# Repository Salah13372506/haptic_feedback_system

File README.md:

# Système de Retour Haptique avec Vision par Ordinateur

## Description du Projet

Projet réalisé dans le cadre du Master Systems for Rehabilitation (MSR) - Sorbonne Université.

Ce système d'assistance innovant a été conçu pour aider les personnes non-voyantes dans leur déplacement quotidien. Il combine la vision par ordinateur et le retour haptique pour détecter les obstacles et communiquer leur position à l'utilisateur via des vibrations. Développé initialement comme un système d'évitement d'obstacles, le projet a le potentiel d'évoluer vers une solution complète de navigation assistée.
Le système utilise une caméra de profondeur OAK-D pour détecter les obstacles et transmet l'information via des moteurs vibrants positionnés de manière ergonomique, permettant à l'utilisateur de percevoir intuitivement la direction des obstacles et de choisir un chemin sûr.
Ce projet s'inscrit dans une démarche d'innovation technologique au service de l'autonomie des personnes en situation de handicap visuel.

## Table des Matières

1. [Vue d'ensemble](#vue-densemble)
2. [Installation](#installation)
3. [Configuration de l'Espace de Travail](#configuration-de-lespace-de-travail)
4. [Nœuds ROS2](#nœuds-ros2)
5. [Partie Électronique](#partie-électronique)
6. [Partie Mécanique](#partie-mécanique)
7. [Documentation Utilisateur](#documentation-utilisateur)

## Vue d'ensemble

Ce projet implémente un système de détection d'obstacles et de retour haptique guidé par vision par ordinateur. Il utilise ROS2, une caméra de profondeur OAK-D, et des moteurs vibrants LRA (Linear Resonant Actuator) contrôlés par une carte Arduino MKR WiFi 1010.

## Installation

### Prérequis Système
- Ubuntu 22.04 LTS
- Python 3.10 ou supérieur
- Git
- VS Code avec PlatformIO

### ROS2 Humble
```bash
wget -c https://raw.githubusercontent.com/ros/rosdistro/master/ros.key && sudo apt-key add ros.key && sudo sh -c 'echo "deb [arch=amd64] http://packages.ros.org/ros2/ubuntu jammy main" > /etc/apt/sources.list.d/ros2.list' && sudo apt update && sudo apt install ros-humble-desktop-full
```

### Configuration Caméra OAK-D

1. Documentation officielle :
   - [Documentation Luxonis OAK-D](https://docs.luxonis.com/projects/api/en/latest/)
   - [Exemples DepthAI](https://github.com/luxonis/depthai-python/tree/main/examples)

2. Installation des dépendances :
   ```bash
   # Installation des dépendances système DepthAI
   sudo wget -qO- https://docs.luxonis.com/install_dependencies.sh | bash

   # Installation de la bibliothèque Python DepthAI
   python3 -m pip install depthai

   # Installation des dépendances ROS2
   sudo apt install ros-humble-depthai-ros
   ```

3. Test de l'installation :
   ```bash
   # Cloner les exemples
   git clone https://github.com/luxonis/depthai-python.git
   cd depthai-python/examples
   
   # Installer les dépendances Python
   python3 install_requirements.py
   
   # Tester la caméra
   python3 ColorCamera/rgb_preview.py
   ```

4. Vérification des règles udev :
   ```bash
   # Vérifier que la caméra est détectée
   lsusb | grep MyriadX
   
   # Si nécessaire, recharger les règles udev
   sudo udevadm control --reload-rules
   sudo udevadm trigger
   ```

### Configuration Arduino et PlatformIO (À lancer avant ROS2)

1. Installation de l'environnement de développement :
   ```bash
   # Installation de VS Code
   sudo apt update
   sudo apt install software-properties-common apt-transport-https wget
   wget -q https://packages.microsoft.com/keys/microsoft.asc -O- | sudo apt-key add -
   sudo add-apt-repository "deb [arch=amd64] https://packages.microsoft.com/repos/vscode stable main"
   sudo apt update
   sudo apt install code
   ```

2. Configuration de PlatformIO :
   - Ouvrir VS Code
   - Aller dans Extensions (Ctrl+Shift+X)
   - Rechercher "PlatformIO IDE"
   - Installer l'extension
   - Redémarrer VS Code

3. Structure du projet Arduino :
   ```
   haptic-arduino/
   ├── platformio.ini
   ├── src/
   │   └── main.cpp              # Code principal Arduino
   ├── lib/
   │   ├── Haptic_DRV2605/      # Bibliothèque des moteurs
   │   └── README.md
   └── include/
       └── README.md
   ```

4. Configuration détaillée dans `platformio.ini` :
   ```ini
   [env:mkrwifi1010]
   platform = atmelsam
   board = mkrwifi1010
   framework = arduino
   
   ; Configuration moniteur série
   monitor_speed = 115200
   monitor_flags = 
       --parity
       N
       --encoding
       UTF-8
   
   ; Dépendances externes
   lib_deps =
       arduino-libraries/WiFiNINA @ ^1.8.14
       bblanchon/ArduinoJson @ ^6.21.3
       Wire
       adafruit/Adafruit DRV2605 Library @ ^1.1.2
   
   ; Options de build
   build_flags =
       -D DEBUG_MODE
       -D WIFI_SSID=\"HapticArduino\"
       -D WIFI_PASS=\"haptic123\"
   
   ; Configuration mémoire
   board_build.f_cpu = 48000000L
   upload_speed = 115200
   ```

5. Compilation et téléversement :
   ```bash
   # Dans le dossier du projet Arduino
   pio run -t upload
   ```

6. Vérification du fonctionnement :
   ```bash
   # Ouvrir le moniteur série
   pio device monitor
   ```
   - Vérifier que l'Arduino crée bien le point d'accès WiFi
   - Confirmer l'initialisation des moteurs
   - Noter l'adresse IP (par défaut 192.168.4.1)

## Nœuds ROS2

### Objectifs des Nœuds

#### 1. Nœud Processeur de Profondeur (processor_node.py)
Ce nœud reçoit les données brutes de la caméra de profondeur et les traite pour identifier les obstacles.
Il normalise les données de profondeur et publie une image traitée où les obstacles proches sont plus sombres.

#### 2. Nœud de Projection 2D (2d.py)
Ce nœud transforme l'image de profondeur traitée en une projection 2D avec détection d'obstacles.
Il analyse la position des obstacles et détermine de quel côté l'utilisateur doit se diriger.

#### 3. Nœud de Publication Haptique (haptic_publisher.py)
Ce nœud gère l'activation des différents moteurs haptiques selon les commandes reçues.
Il maintient deux groupes de moteurs (gauche et droite) et coordonne leurs activations.

#### 4. Nœud Bridge WiFi (wifi_bridge.py)
Ce nœud établit la communication WiFi entre ROS2 et l'Arduino.
Il convertit les commandes ROS2 en messages JSON et les envoie à l'Arduino via UDP.

### Lancement des Nœuds

#### 1. Lancement de la Caméra
```bash
# Lance la caméra OAK-D et publie les données de profondeur
colcon build --symlink-install --packages-select depthai_bridge
colcon build --symlink-install --packages-select depthai_examples
source install/setup.bash
ros2 launch depthai_examples stereo_inertial_node.launch.py depth:=true
```

#### 2. Lancement des Nœuds de Traitement
```bash
# Compile et lance les nœuds de traitement de profondeur
colcon build --packages-select depth_processor
source install/setup.bash
ros2 run depth_processor processor_node
ros2 run depth_processor 2d_node
```

#### 3. Lancement des Nœuds Haptiques
```bash
# Compile et lance les nœuds de contrôle haptique
colcon build --packages-select haptic_control_interfaces haptic_control_pkg
source install/setup.bash
ros2 run haptic_control_pkg haptic_publisher
ros2 run haptic_control_pkg haptic_bridge
```

### Tests Rapides
```bash
# Active les moteurs gauches
ros2 topic pub /haptic_side haptic_control_interfaces/msg/SideCommand "{side: 2}"

# Active les moteurs droits
ros2 topic pub /haptic_side haptic_control_interfaces/msg/SideCommand "{side: 1}"
```

## Partie Électronique

### Liste du Matériel
- 1x Arduino MKR WiFi 1010
- 8x Moteurs LRA
- 1x Multiplexeur I2C TCA9548A
- 8x Drivers DRV2605
- 1x PCB personnalisée
- Composants:
  - Régulateur 3.3V
  - Condensateurs de découplage
  - Résistances pull-up
  - Connecteurs moteurs

### Carte PCB

La carte PCB a été conçue pour gérer 6 moteurs haptiques de type LRA. Elle intègre les composants suivants :

#### Composants Principaux
- 1x Arduino MKR WiFi 1010 (microcontrôleur principal)
- 6x Drivers DRV2605 (contrôle des moteurs LRA)
- 1x Multiplexeur I2C TCA9548A (gestion des multiples drivers)
- 6x Connecteurs JST femelles (connexion des moteurs)

#### Connexions
- Chaque moteur se connecte via un connecteur JST 2 pins pour :
  - VCC (alimentation)
  - GND (masse)

#### Communication
- Bus I2C distribué via le multiplexeur
- Le multiplexeur permet de gérer les 6 drivers avec une seule paire de lignes I2C

*Note : Tous les fichiers liés à la PCB sont disponibles dans le dossier `PCB_designing/` du projet*

### Configuration WiFi Arduino
- Mode: Point d'accès (AP)
- SSID: "HapticArduino"
- Password: "haptic123"
- IP Arduino: 192.168.4.1
- Port UDP: 8888
- Format: JSON

### Format des Messages JSON
```json
{
    "motor": 0-7,           // ID du moteur
    "waveform": 0-123,      // Pattern de vibration
    "activate": true/false,  // Activation/désactivation
    "intensity": 0.0-1.0    // Intensité de vibration
}
```

## Partie Mécanique

Le système comporte plusieurs pièces imprimées en 3D, chacune ayant une fonction spécifique :

### 1. Support Principal
- Pièce servant de base au système
- Conçue avec un système de clips pour maintenir la PCB
- Intègre un couvercle arrière pour protéger l'électronique
- Dimensions optimisées pour s'adapter à la PCB et au boîtier de la caméra

### 2. Support Moteur et Driver (Prototype)
- Prototype initial permettant d'accueillir :
  - Le moteur LRA
  - Son driver DRV2605
  - Les connexions nécessaires
- Bien que non utilisé dans la version finale, ce design reste pertinent pour des tests unitaires ou des prototypes

### 3. Support Moteur Simple
- Version optimisée pour maintenir uniquement le moteur LRA
- Design minimaliste pour réduire l'encombrement
- Système de fixation sécurisé pour le moteur
- Adapté pour l'intégration dans le système final

*Note : Tous les fichiers STL et les sources CAO sont disponibles dans le dossier `Solidworks/` du projet*

## Documentation Utilisateur

[Manuel Utilisateur PDF](lien_vers_manuel.pdf)

## Résolution des Problèmes

### Caméra non détectée
- Vérifier connexion USB
- Vérifier règles udev
- Redémarrer le service udev

### Erreurs WiFi
- Vérifier que l'Arduino crée bien le point d'accès
- Vérifier dans le moniteur série (115200 baud) le statut de la connexion
- Confirmer l'IP et le port dans le code

### Moteurs non réactifs
- Vérifier l'adresse du multiplexeur I2C (0x70)
- Vérifier les connexions des moteurs
- Utiliser le moniteur série pour voir les messages d'initialisation

## Contact
Pour toute question sur ce projet, contactez les auteurs via LinkedIn.

## Auteurs et Remerciements

### Auteurs
- Amal BECHEKER
- Salah Eddine HAMIZI
- Vincent FONROUGE

### Remerciements
Nous tenons à remercier particulièrement :
- M. Fabien VÉRITÉ pour la gestion et la coordination du Master MSR
- L'équipe pédagogique de Sorbonne Université

Projet réalisé dans le cadre du Master MSR - Sorbonne Université, 2024.

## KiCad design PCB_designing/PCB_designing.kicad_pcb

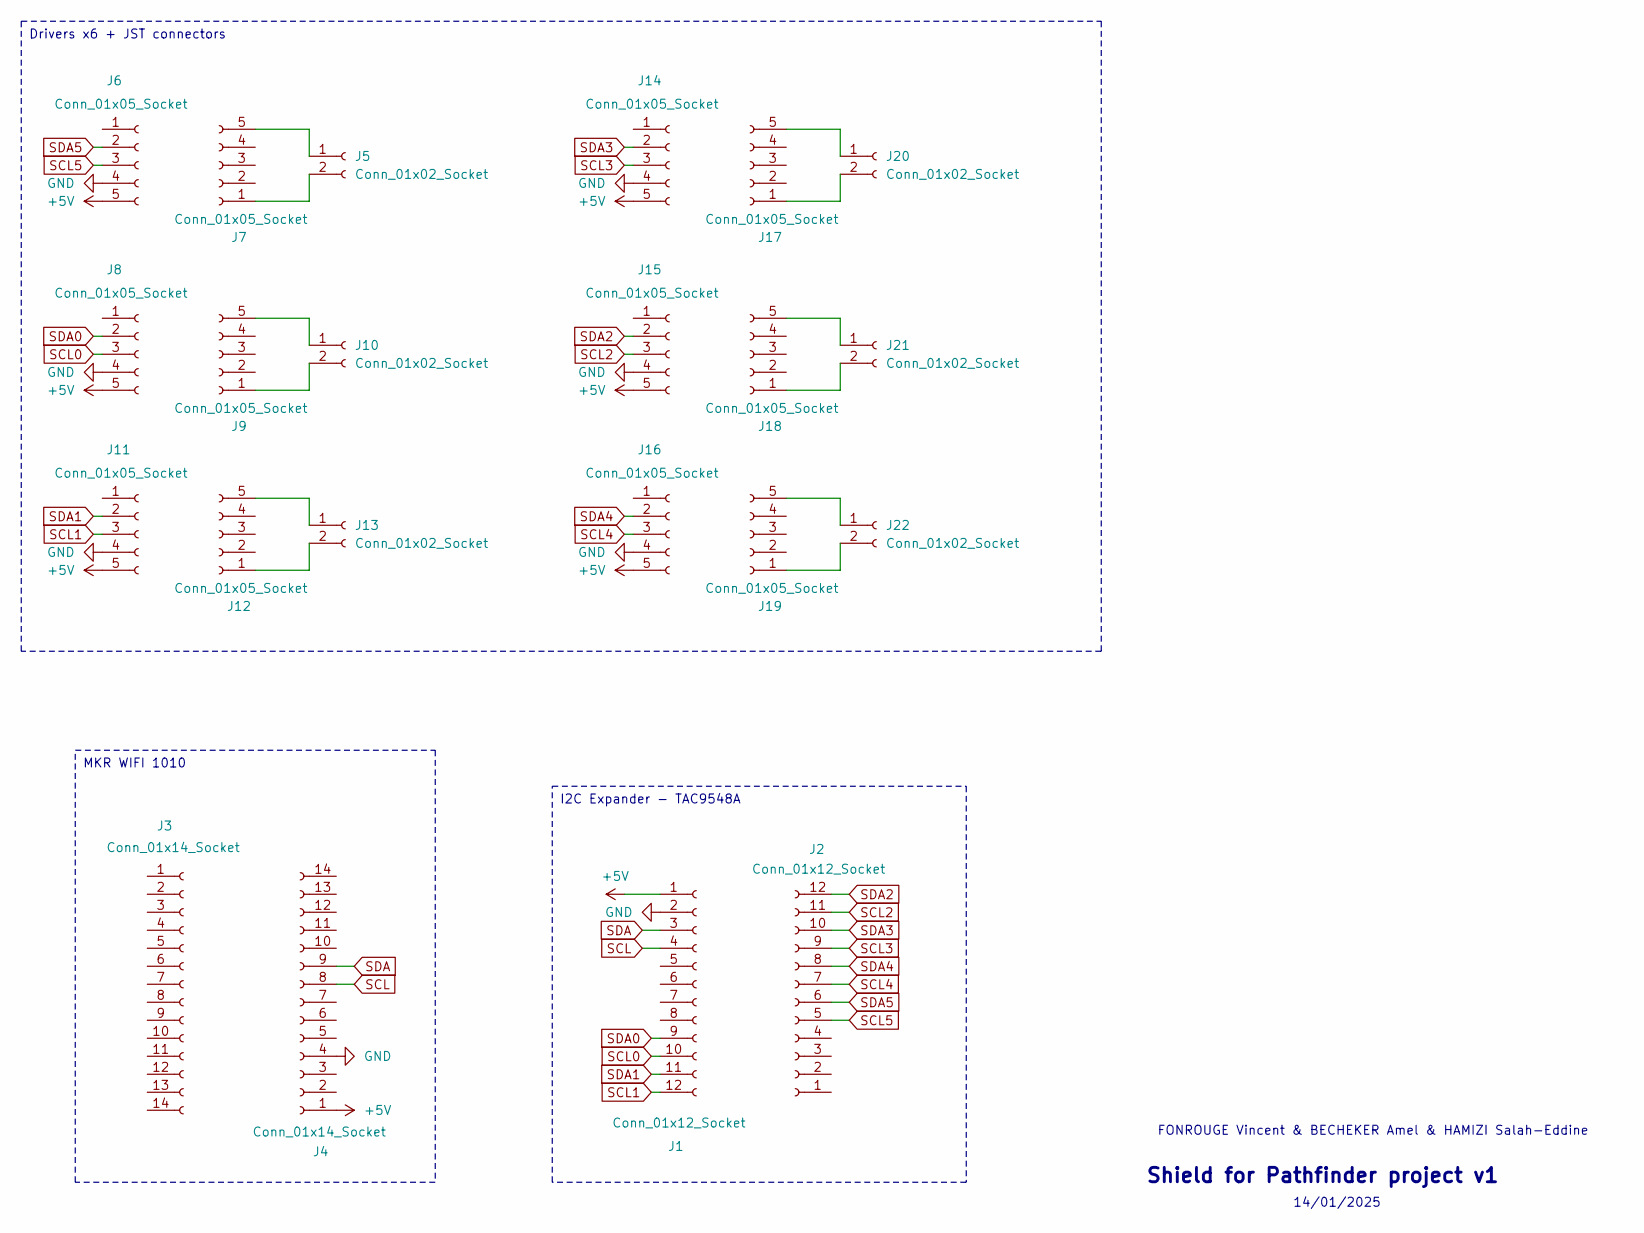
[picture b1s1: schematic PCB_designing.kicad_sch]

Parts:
J1, J2: Conn_01x12_Socket; PinSocket_1x12_P2.54mm_Vertical
J3, J4: Conn_01x14_Socket; PinSocket_1x14_P2.54mm_Vertical
J5, J10, J13, J20, J21, J22: Conn_01x02_Socket; JST_EH_S2B-EH_1x02_P2.50mm_Horizontal
J6, J7, J8, J9, J11, J12, J14, J15, J16, J17, J18, J19: Conn_01x05_Socket; PinSocket_1x05_P2.54mm_Vertical

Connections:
+5V: J1.1, J4.1, J6.5, J8.5, J11.5, J14.5, J15.5, J16.5
GND: J1.2, J4.4, J6.4, J8.4, J11.4, J14.4, J15.4, J16.4
unnamed: J5.1, J7.5
unnamed: J5.2, J7.1
unnamed: J9.5, J10.1
unnamed: J9.1, J10.2
unnamed: J12.1, J13.2
unnamed: J12.5, J13.1
unnamed: J17.1, J20.2
unnamed: J17.5, J20.1
unnamed: J18.1, J21.2
unnamed: J18.5, J21.1
unnamed: J19.1, J22.2
unnamed: J19.5, J22.1
SCL: J1.4, J4.8
SCL0: J1.10, J8.3
SCL1: J1.12, J11.3
SCL2: J2.11, J15.3
SCL3: J2.9, J14.3
SCL4: J2.7, J16.3
SCL5: J2.5, J6.3
SDA: J1.3, J4.9
SDA0: J1.9, J8.2
SDA1: J1.11, J11.2
SDA2: J2.12, J15.2
SDA3: J2.10, J14.2
SDA4: J2.8, J16.2
SDA5: J2.6, J6.2

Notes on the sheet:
Drivers x6 + JST connectors
MKR WIFI 1010
I2C Expander - TAC9548A
FONROUGE Vincent & BECHEKER Amel & HAMIZI Salah-Eddine
Shield for Pathfinder project v1
14/01/2025

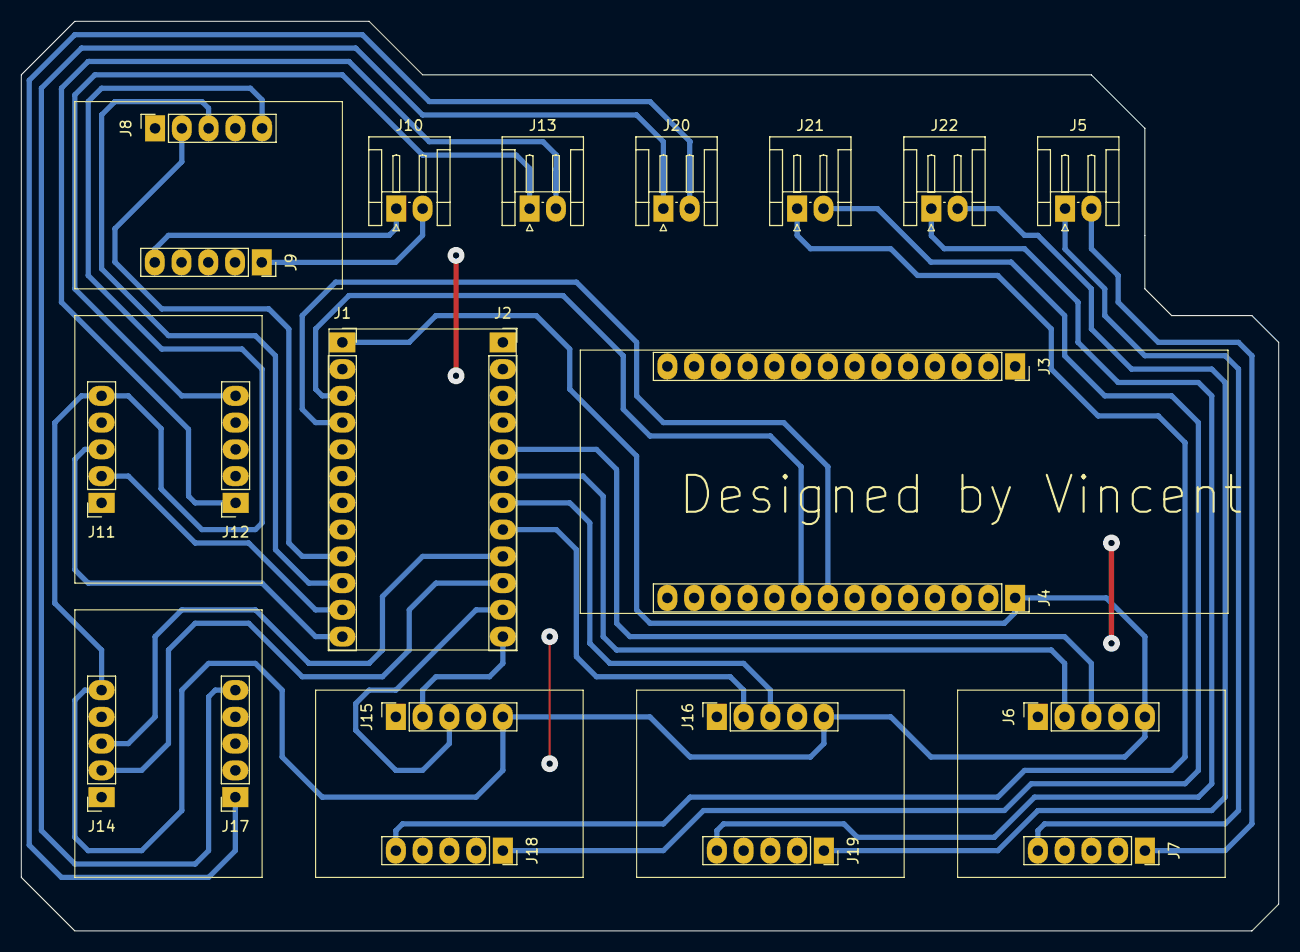
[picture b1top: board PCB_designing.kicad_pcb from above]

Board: 2 copper layers, 119.4 x 86.4 mm, 22 parts (0 on the bottom side), 28 nets.

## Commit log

2025-01-04 Initial commit: Add ROS2 packages and Arduino code
2025-01-04 Add README
2025-01-20 Update README.md
    first change not final
2025-01-20 Update README.md
    images
